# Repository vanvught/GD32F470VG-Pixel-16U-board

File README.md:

See latest [https://github.com/vanvught/Kicad-GD32F470VG-Pixel-16](https://github.com/vanvught/Kicad-GD32F470VG-Pixel-16)

# Archived

Features: 

- 16x 4 Universes pixel output
- 1x SPI Flash ROM for storing the configuration and Art-Net Fail-safe record
- 1x I2C (display)
- 1x UART (programming/debug)

Firmware: [https://github.com/vanvught/GD32F470VG-Pixel-16U](https://github.com/vanvught/GD32F470VG-Pixel-16U)

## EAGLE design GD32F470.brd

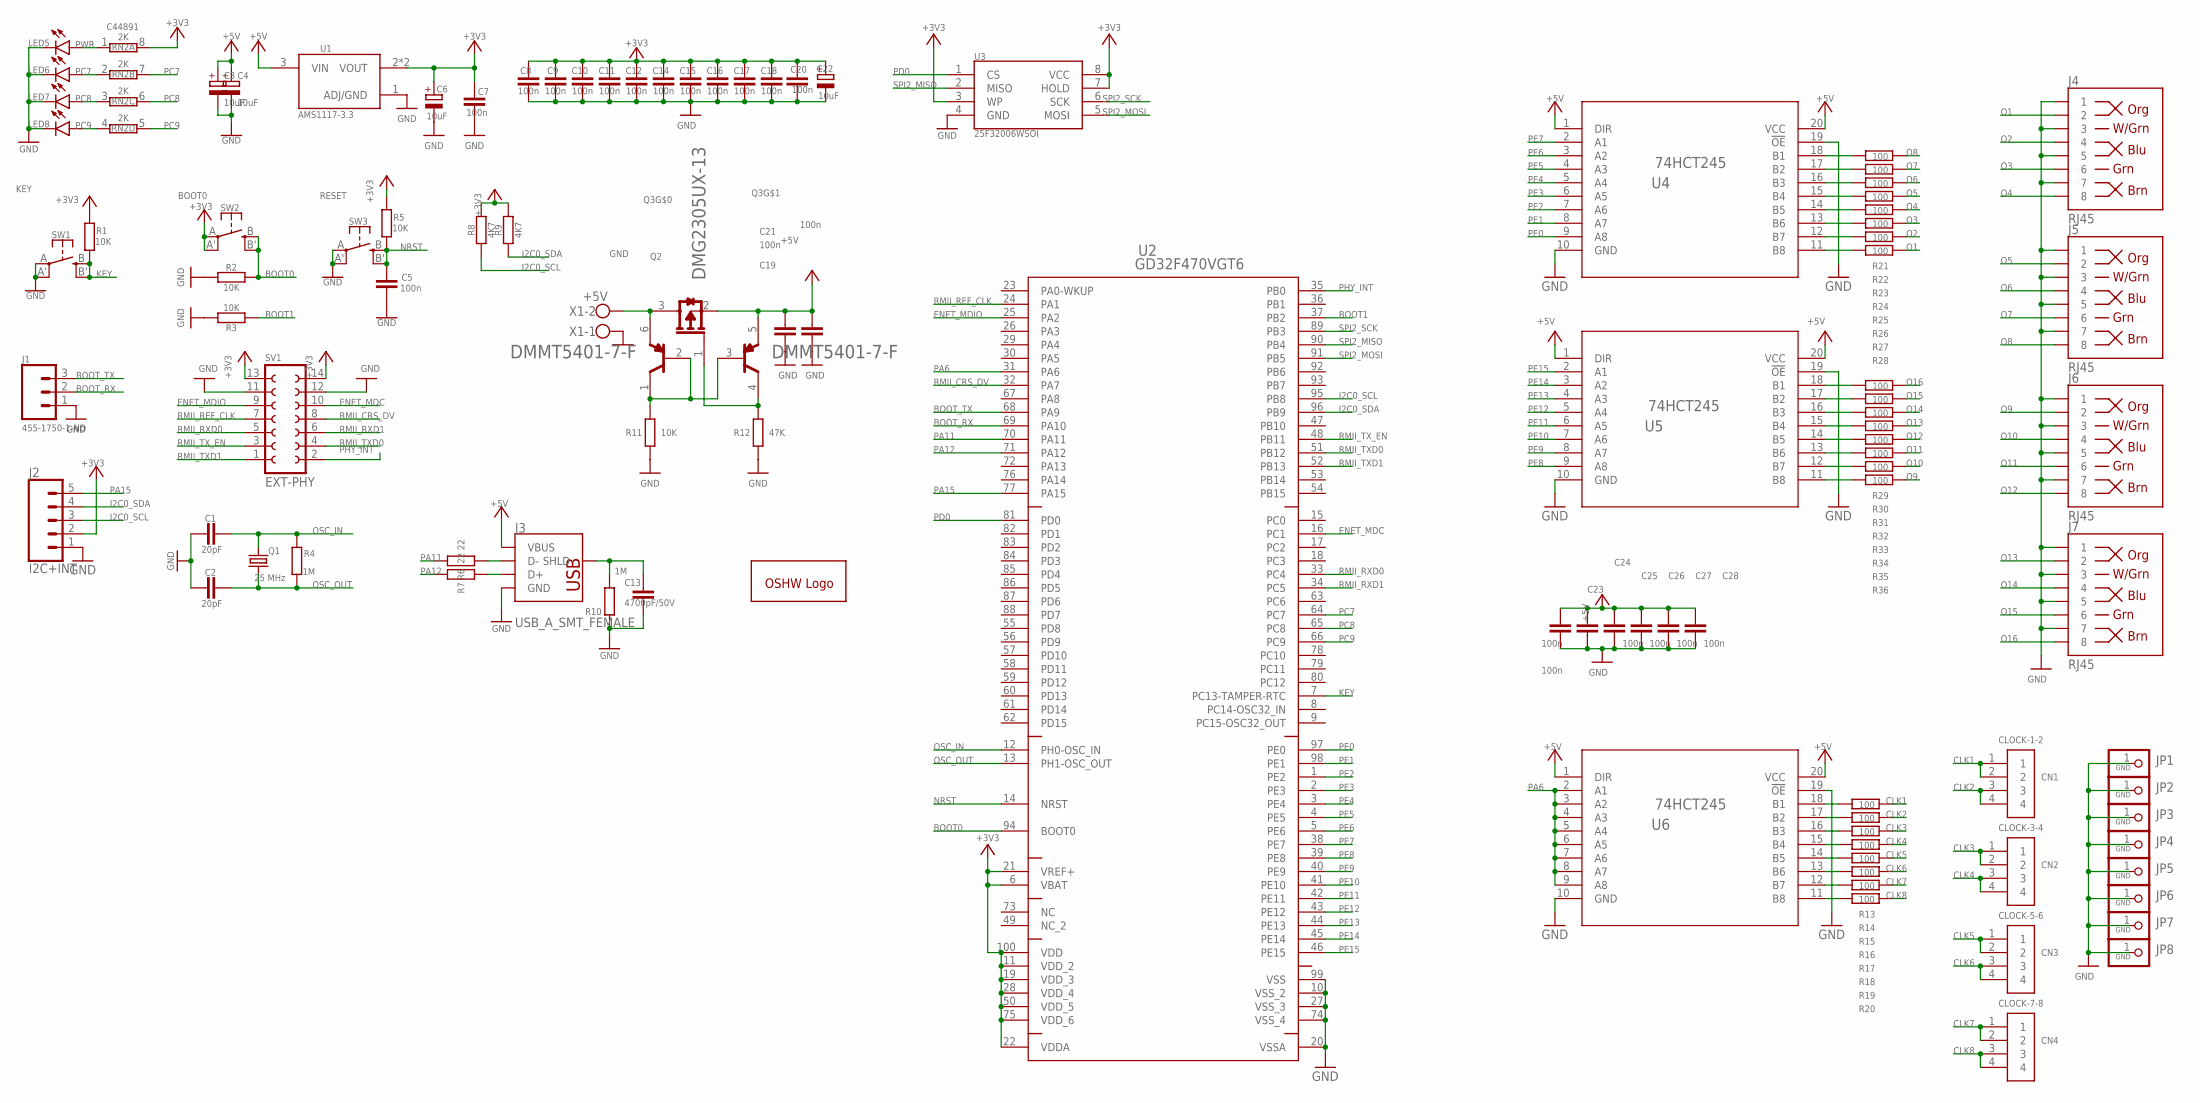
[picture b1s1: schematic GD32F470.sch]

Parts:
C1, C2: 20pF; C0603; JLCPCB C38523
C3, C4, C6, C22: 10uF; A/3216-18R; JLCPCB C7171
C5, C7, C8, C9, C10, C11, C12, C14, C15, C16, C17, C18, C20, C23, C24, C25, C26, C27, C28: 100n; C0603; JLCPCB C14663
C13: 4700pF/50V; C0603
C19, C21: 100n; C0603
CN1: CLOCK-1-2; 1X04-CLEANBIG
CN2: CLOCK-3-4; 1X04-CLEANBIG
CN3: CLOCK-5-6; 1X04-CLEANBIG
CN4: CLOCK-7-8; 1X04-CLEANBIG
GOLD_ORB_SM1: OSHWLOGOLOGO5MM; OSHW_5MM
J1: 455-1750-1-ND; 1X03
J2: I2C+INT; 1X05
J3: USB_A_SMT_FEMALE; USB-A
J4, J5, J6, J7: RJ45; RJ45-8
JP1, JP2, JP3, JP4, JP5, JP6, JP7, JP8: GND; 1X01-CLEANBIG
LED5: PWR; CHIP-LED0603
LED6: PC7; CHIP-LED0603
LED7: PC8; CHIP-LED0603
LED8: PC9; CHIP-LED0603
Q1: 25 MHz; CSM-7X-DU; JLCPCB C14872
Q2: DMG2305UX; DIODES_INC._DMG2305UX-13_0
Q3: DMMT5401; DIODES_DMMT5401-7-F_0
R1, R2, R3, R5: 10K; R0603; JLCPCB C25804
R4: 1M; R0603; JLCPCB C22935
R6, R7: 22; R0402
R8, R9: 4K7; R0402; JLCPCB C23162
R10: 1M; R0603
R11: 10K; R0402
R12: 47K; R0402
R13, R14, R15, R16, R17, R18, R19, R20, R21, R22, R23, R24, R25, R26, R27, R28, R29, R30, R31, R32, R33, R34, R35, R36: 100; R0402
RN2: 2K; 4X0402ARV341; JLCPCB C44891
SV1: EXT-PHY; FE07-2W
SW1: KEY; EVQ-Q2
SW2: BOOT0; EVQ-Q2; JLCPCB C221880
SW3: RESET; EVQ-Q2
U1: AMS1117-3.3; SOT229P700X180-4N
U2: GD32F470VGT6; LQFP100
U3: 25F32006WSOI; SO08-EIAJ; JLCPCB C97521
U4, U5, U6: 74HCT245; PW20
X1: +5V; W237-102

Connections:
+3V3: C6.+, C7.1, C8.1, C9.1, C10.1, C11.1, C12.1, C14.1, C15.1, C16.1, C17.1, C18.1, C20.1, C22.+, J2.2, R1.2, R5.2, R8.2, R9.2, RN2.8 (2), SV1.13, SV1.14, SW2.A, SW2.A' (P1), U1.2 (VOUT), U1.4 (VOUT), U2.6 (VBAT), U2.11 (VDD_2), U2.19 (VDD_3), U2.21 (VREF+), U2.22 (VDDA), U2.28 (VDD_4), U2.50 (VDD_5), U2.75 (VDD_6), U2.100 (VDD), U3.3 (WP), U3.7 (HOLD), U3.8 (VCC)
+5V: C3.+, C4.+, C19.1, C21.1, C23.1, C24.1, C25.1, C26.1, C27.1, C28.1, J3.VBUS, Q2.2 (S), Q3.5 (E2), U1.3 (VIN), U4.1 (DIR), U4.20 (VCC), U5.1 (DIR), U5.20 (VCC), U6.1 (DIR), U6.20 (VCC)
BOOT0: R2.2, SW2.B (S), SW2.B' (S1), U2.94 (BOOT0)
BOOT1: R3.1, U2.37 (PB2)
BOOT_RX: J1.2, U2.69 (PA10)
BOOT_TX: J1.3, U2.68 (PA9)
CLK1: CN1.1, CN1.2, R13.2
CLK2: CN1.3, CN1.4, R14.2
CLK3: CN2.1, CN2.2, R15.2
CLK4: CN2.3, CN2.4, R16.2
CLK5: CN3.1, CN3.2, R17.2
CLK6: CN3.3, CN3.4, R18.2
CLK7: CN4.1, CN4.2, R19.2
CLK8: CN4.3, CN4.4, R20.2
ENET_MDC: SV1.10, U2.16 (PC1)
ENET_MDIO: SV1.9, U2.25 (PA2)
GND: C1.1, C2.1, C3.-, C4.-, C5.2, C6.-, C7.2, C8.2, C9.2, C10.2, C11.2, C12.2, C13.2, C14.2, C15.2, C16.2, C17.2, C18.2, C19.2, C20.2, C21.2, C22.-, C23.2, C24.2, C25.2, C26.2, C27.2, C28.2, J1.1, J2.1, J3.GND, J4.1, J4.3, J4.5, J4.7, J5.1, J5.3, J5.5, J5.7, J6.1, J6.3, J6.5, J6.7, J7.1, J7.3, J7.5, J7.7, JP1.1, JP2.1, JP3.1, JP4.1, JP5.1, JP6.1, JP7.1, JP8.1, LED5.C, LED6.C, LED7.C, LED8.C, R2.1, R3.2, R10.1, R11.1, R12.1, SV1.11, SV1.12, SW1.A, SW1.A' (P1), SW3.A, SW3.A' (P1), U1.1 (ADJ/GND), U2.10 (VSS_2), U2.20 (VSSA), U2.27 (VSS_3), U2.74 (VSS_4), U2.99 (VSS), U3.4 (GND), U4.10 (GND), U4.19 (!OE), U5.10 (GND), U5.19 (!OE), U6.10 (GND), U6.19 (!OE), X1.1
I2C0_SCL: J2.3, R8.1, U2.95 (PB8)
I2C0_SDA: J2.4, R9.1, U2.96 (PB9)
KEY: R1.1, SW1.B (S), SW1.B' (S1), U2.7 (PC13-TAMPER-RTC)
unnamed: R21.1, U4.18 (B1)
unnamed: Q3.1 (C1), Q3.2 (B1), Q3.3 (B2), R11.2
unnamed: R22.1, U4.17 (B2)
unnamed: R23.1, U4.16 (B3)
unnamed: R24.1, U4.15 (B4)
unnamed: R25.1, U4.14 (B5)
unnamed: R26.1, U4.13 (B6)
unnamed: R27.1, U4.12 (B7)
unnamed: R28.1, U4.11 (B8)
unnamed: R29.1, U5.18 (B1)
unnamed: R30.1, U5.17 (B2)
unnamed: R31.1, U5.16 (B3)
unnamed: R32.1, U5.15 (B4)
unnamed: R33.1, U5.14 (B5)
unnamed: R34.1, U5.13 (B6)
unnamed: R35.1, U5.12 (B7)
unnamed: R36.1, U5.11 (B8)
unnamed: J3.D-, R6.1
unnamed: LED5.A, RN2.1
unnamed: LED6.A, RN2.2 (1)
unnamed: LED7.A, RN2.3 (1)
unnamed: LED8.A, RN2.4 (1)
unnamed: Q2.1 (G), Q3.4 (C2), R12.2
unnamed: Q2.3 (D), Q3.6 (E1), X1.2
unnamed: R13.1, U6.18 (B1)
unnamed: R14.1, U6.17 (B2)
unnamed: R15.1, U6.16 (B3)
unnamed: R16.1, U6.15 (B4)
unnamed: R17.1, U6.14 (B5)
unnamed: R18.1, U6.13 (B6)
unnamed: R19.1, U6.12 (B7)
unnamed: R20.1, U6.11 (B8)
unnamed: J3.D+, R7.1
NRST: C5.1, R5.1, SW3.B (S), SW3.B' (S1), U2.14 (NRST)
O1: J4.2, R28.2
O2: J4.4, R27.2
O3: J4.6, R26.2
O4: J4.8, R25.2
O5: J5.2, R24.2
O6: J5.4, R23.2
O7: J5.6, R22.2
O8: J5.8, R21.2
O9: J6.2, R36.2
O10: J6.4, R35.2
O11: J6.6, R34.2
O12: J6.8, R33.2
O13: J7.2, R32.2
O14: J7.4, R31.2
O15: J7.6, R30.2
O16: J7.8, R29.2
OSC_IN: C1.2, Q1.2, R4.1, U2.12 (PH0-OSC_IN)
OSC_OUT: C2.2, Q1.1, R4.2, U2.13 (PH1-OSC_OUT)
PA6: U2.31 (PA6), U6.2 (A1), U6.3 (A2), U6.4 (A3), U6.5 (A4), U6.6 (A5), U6.7 (A6), U6.8 (A7), U6.9 (A8)
PA11: R6.2, U2.70 (PA11)
PA12: R7.2, U2.71 (PA12)
PA15: J2.5, U2.77 (PA15)
PC7: RN2.7 (2), U2.64 (PC7)
PC8: RN2.6 (2), U2.65 (PC8)
PC9: RN2.5 (2), U2.66 (PC9)
PD0: U2.81 (PD0), U3.1 (CS)
PE0: U2.97 (PE0), U4.9 (A8)
PE1: U2.98 (PE1), U4.8 (A7)
PE2: U2.1 (PE2), U4.7 (A6)
PE3: U2.2 (PE3), U4.6 (A5)
PE4: U2.3 (PE4), U4.5 (A4)
PE5: U2.4 (PE5), U4.4 (A3)
PE6: U2.5 (PE6), U4.3 (A2)
PE7: U2.38 (PE7), U4.2 (A1)
PE8: U2.39 (PE8), U5.9 (A8)
PE9: U2.40 (PE9), U5.8 (A7)
PE10: U2.41 (PE10), U5.7 (A6)
PE11: U2.42 (PE11), U5.6 (A5)
PE12: U2.43 (PE12), U5.5 (A4)
PE13: U2.44 (PE13), U5.4 (A3)
PE14: U2.45 (PE14), U5.3 (A2)
PE15: U2.46 (PE15), U5.2 (A1)
PHY_INT: SV1.2, U2.35 (PB0)
RMII_CRS_DV: SV1.8, U2.32 (PA7)
RMII_REF_CLK: SV1.7, U2.24 (PA1)
RMII_RXD0: SV1.5, U2.33 (PC4)
RMII_RXD1: SV1.6, U2.34 (PC5)
RMII_TXD0: SV1.4, U2.51 (PB12)
RMII_TXD1: SV1.1, U2.52 (PB13)
RMII_TX_EN: SV1.3, U2.48 (PB11)
SHLD: C13.1, J3.SHLD1 (SHLD), J3.SHLD2 (SHLD), R10.2
SPI2_MISO: U2.90 (PB4), U3.2 (MISO)
SPI2_MOSI: U2.91 (PB5), U3.5 (MOSI)
SPI2_SCK: U2.89 (PB3), U3.6 (SCK)

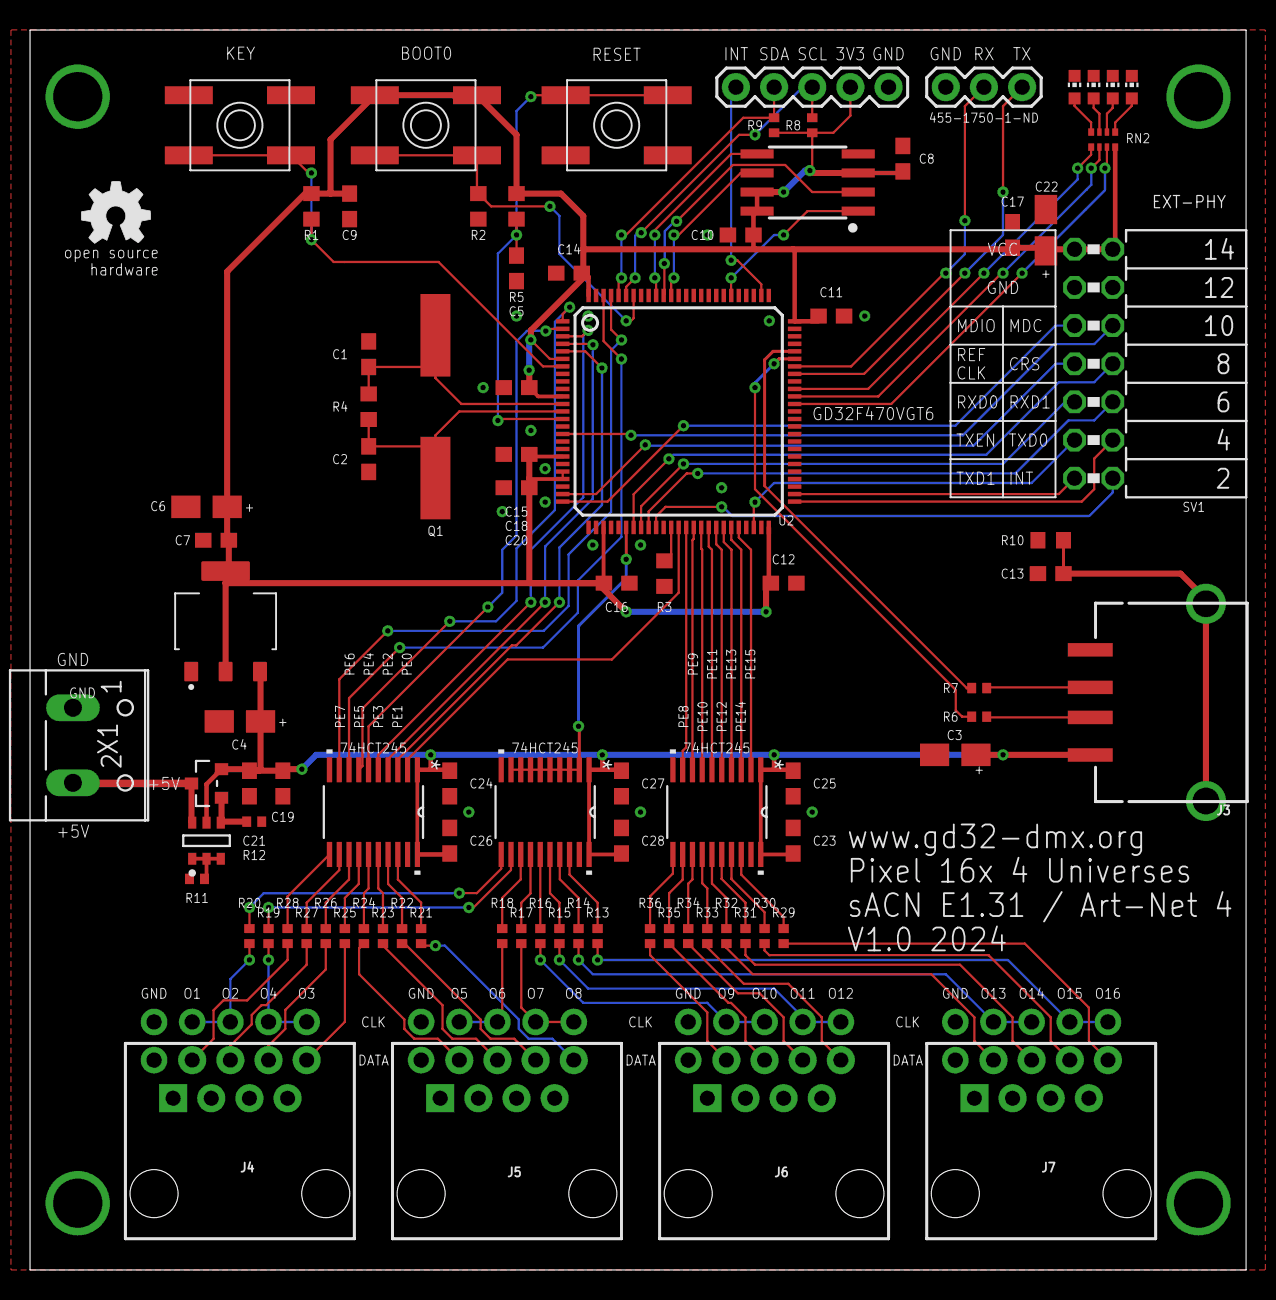
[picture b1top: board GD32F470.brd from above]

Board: 2 copper layers, 81.0 x 82.5 mm, 103 parts (0 on the bottom side), 108 nets.

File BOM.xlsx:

Qty | Designator | Footprint | Comment | LCSC Part #
2 | C1, C2 | C0603 | 20pF | C1648
1 | C13 | C0603 | 4700pF/50V | C53987
4 | C3, C4, C6, C22 | A/3216-18R | 10uF | C7171
21 | C5, C7, C8, C9, C10, C11, C12, C14, C15, C16, C17, C18, C19, C20, C21, C23, C24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 | C0603 | 100n | C14663
1 | J3 | USB-A-S-SILK-FEMALE | USB_A_SMT_FEMALE | C668591
4 | LED5,LED6,LED7,LED8 | CHIP-LED0603 | PC0 | C72038
1 | Q1 | CSM-7X-DU | 25 MHz | C14872
1 | Q2 | DIODES_INC._DMG2305UX-13_0 | DMG2305UX | C150470
1 | Q3 | DIODES_DMMT5401-7-F_0 | DMMT5401 | C154733
4 | R1, R2, R3, R5 | R0603 | 10K | C25804
2 | R4, R10 | R0603 | 1M | C22935
1 | R11 | R0402 | 10K | C25744
1 | R12 | R0402 | 47K | C25792
24 | R13, R14, R15, R16, R17, R18, R19, R20, R21, R22, R23, R24, R25, R26, R27, R28,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 | R0402 | 100 | C25076
2 | R6, R7 | R0402 | 22 | C25092
2 | R8, R9 | R0402 | 4K7 | C25900
1 | RN2 | 4X0402ARV341 | 2K | C44891
3 | SW1, SW2, SW3 | EVQ-Q2 | SWITCH | C221880
1 | U1 | SOT229P700X180-4N | AMS1117-3.3 | C6186
1 | U2 | LQFP100 | GD32F470VGT6 | C3029773
1 | U3 | SO08-EIAJ | W25Q128JVSIQ | C97521
3 | U4, U5, U6 | PW20 | 74HCT245 | C10910

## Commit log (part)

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2026-03-11 Replace USB-A footprint
    Swap SparkFun USB-A footprint for a local GD32F USB-A (new library/packages and 3D package), update footprint URNs/library_version for multiple parts (1X03, SO08-EIAJ, 1X05, etc.), and adjust board e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
2026-03-20 Add GD32F470 board image and update README
    Add new GD32F470.png board image and expand README with device features, firmware repo link, and embedded image. Improves documentation for the GD32F470 Pixel project and provides quick reference to 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

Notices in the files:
parts and their libraries:
SparkFun-Connectors: Licensing: Creative Commons ShareAlike 4.0 International - https://creativecommons.org/licenses/by-sa/4.0
COPYRIGHT: Copyright (C) 2022 Ultra Librarian. All rights reserved.
